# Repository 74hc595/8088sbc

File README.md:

# 8088 Single Board Computer

A minimal single-board computer based on the Intel 8088 processor.
That's the same processor used in the original IBM PC, but this is just a
simple project and doesn't strive for PC/DOS compatibility.

## Specs
- 8088 or compatible CPU in minimal mode (5 MHz with [8088](https://www.jameco.com/z/8088-Major-Brands-IC-8088-8-Bit-HMOS-MPU_52142.html), 8 MHz with 8088-2)
    - Clock oscillator at 3x frequency of CPU clock frequency. For 8 MHz operation, uses a [24 MHz half-can crystal oscillator](https://www.mouser.com/ProductDetail/ECS/ECS-2200B-240?qs=GxOUx7aO6nwQDraMtk%2FyHw%3D%3D)
- 1 MB static RAM (2x [AS6C4008-55PCN](https://www.mouser.com/ProductDetail/Alliance-Memory/AS6C4008-55PCN?qs=%2Fha2pyFaduhSIt5XfNvHc%2FWglHK486gNG4HA%2F19hDPofxZgoFVNuaw%3D%3D))
- 32 KB ROM (1x [AT28C256-15](https://www.jameco.com/z/28C256-15-Major-Brands-IC-28C256-16-EEPROM-256K-Bit-CMOS-Parallel_74843.html))
- FTDI-compatible 5V serial port provided by a [16C550](https://www.jameco.com/shop/ProductDisplay?catalogId=10001&langId=-1&storeId=10001&productId=288809) UART (up to 115200 baud)
- 32 column by 4 row LED display (sixteen PDSP-1881 intelligent displays,
  display board schematic available [here](https://github.com/74hc595/kicad-intelligent-displays))
- Uses five common 74HC chips for glue logic (74HC4017, 74HC132, 74HC573,
  74HC75, 74HC139). Does not require any of the Intel 8200-series support chips.
- 5V power via USB-A connector

## Memory map

```
00000h-7FFFFh - RAM
80000h-FFFFFh - bankable (RAM, ROM, expansion 1, or expansion 2)
```

## I/O map

Only bits 7 and 8 are used for decoding.

```
000h-07Fh - I/O bank 0
    060h-067h - 16550 UART
080h-0FFh - I/O bank 1
100h-17Fh - I/O bank 2
    100h-107h - 128-character display (16x PDSP-1881 or similar)
180h-1FFh - I/O bank 3
```

More info on display decoding:

```
100h-17Fh - Flash RAM
900h-97Fh - UDC Address Register
B00h-B7Fh - UDC RAM
D00h-D7Fh - Control Word Register
F00h-F7Fh - Character RAM
```

## Bank switching and input/output

The modem control lines of the 16550 UART are used as general purpose input and
output lines.

```
~OUT1 - bank select bit 0
~OUT2 - bank select bit 1
~DTR  - general purpose output 0 (LED2)
~RTS  - general purpose output 1 (LED3)
~RI   - general purpose input 0
~DCD  - general purpose input 1
~DSR  - general purpose input 2
~CTS  - general purpose input 3
```

Bank select bits 0 and 1 control which device is mapped into the upper half of
the address space:

```
00 - expansion 1
01 - expansion 2
10 - RAM
11 - ROM (default at power-up)
```

These are controlled by bits 2 and 3 of the 16550's Modem Control Register.
(`64h`)

## Interrupts

The four general-purpose inputs can be set up as inputs by configuring the
16550's Interrupt Enable Register (`61h`). However, this won't be very useful
because the 8088's `~INTA` line is not connected to anything, so when an
interrupt is received, there is no device to place the vector number on the data
bus.

Pressing the `NMI` button will generate a non-maskable interrupt (`INT 04h`).
The button is debounced in hardware.

## Software

Not much here, just enough to test memory and dump the register state. Compiles
with NASM (version 2.14.02 used). Running `make` in the `code/` directory
generates as 32KB binary file. Running `make flash` can be used to burn the
ROM image to an AT28C256 EEPROM chip using a [MiniPro TL866II+](https://www.amazon.com/tl866ii-plus/s?k=tl866ii+plus)
with the [minipro](https://gitlab.com/DavidGriffith/minipro/) utility.

(The TL866II+ is around $60 USD and widely available, if you don't have one,
you should get one!)

1. Power LED will light up.
2. `OUT1` LED will blink four times. (Testing 8 segments of lower RAM)
3. `OUT0` will light.
4. `OUT1` LED will blink four times. (Testing 8 segments of upper RAM)
5. `Hello 8088!` will be printed to the serial port. (115200 8N1)
6. `OUT0` and `OUT1` LEDs will toggle with 50% duty cycle. (verify with scope)
7. Pressing the `NMI` button will print the register state:

```
AX=F001 CS=F000 IP=82E0      NMI
BX=FFF0 DS=F000 SI=82F5     --I-
CX=0000 ES=0000 DI=0024 --------
DX=F202 SS=7000 SP=FFE6 BP=FFFF
```

### API

Interrupt vector `06h` points to the character output routine. If using the
PDSP-1881 LED display, this can be changed to `disp_outch_int` to write to the
display instead of the serial port.

`INT 07h` prints the null-terminated string in `CS:SI`.

`INT 08h` is a rudimentary formatted-output routine. See `output.inc`.

## Future work

Probably none. This was just a quick project and I probably won't work on it
long-term because... honestly, I'm just not a fan of 8086 assembly language and
its weird 16-bit segmented model. Mainly, I had these chips lying around and
wanted to do something with them.

## About

Open hardware, released under the terms of the 3-clause BSD license.

Copyright 2020 Matt Sarnoff.

http://twitter.com/txsector

http://msarnoff.org

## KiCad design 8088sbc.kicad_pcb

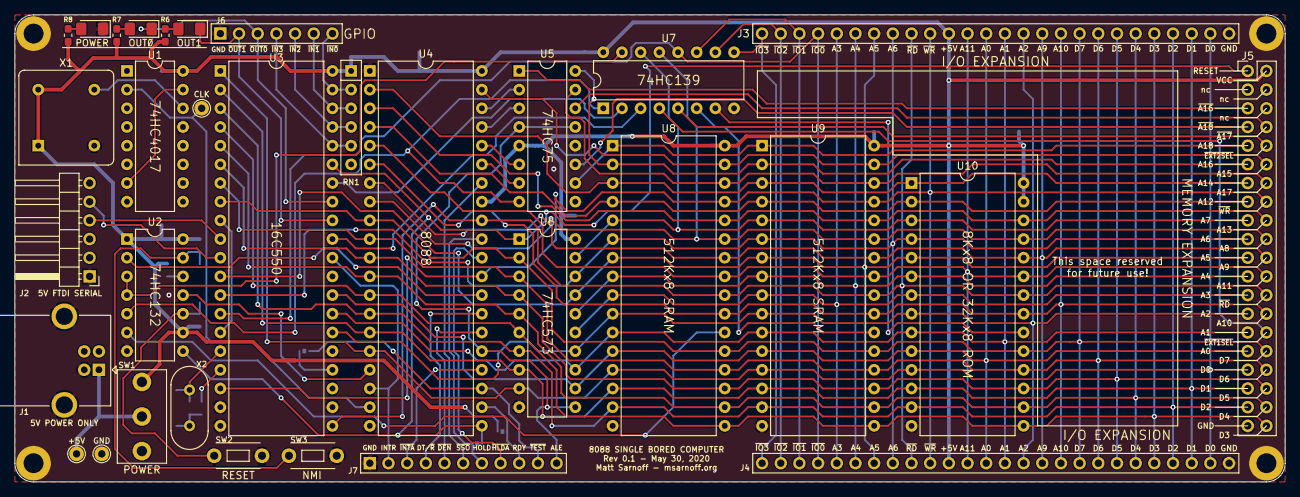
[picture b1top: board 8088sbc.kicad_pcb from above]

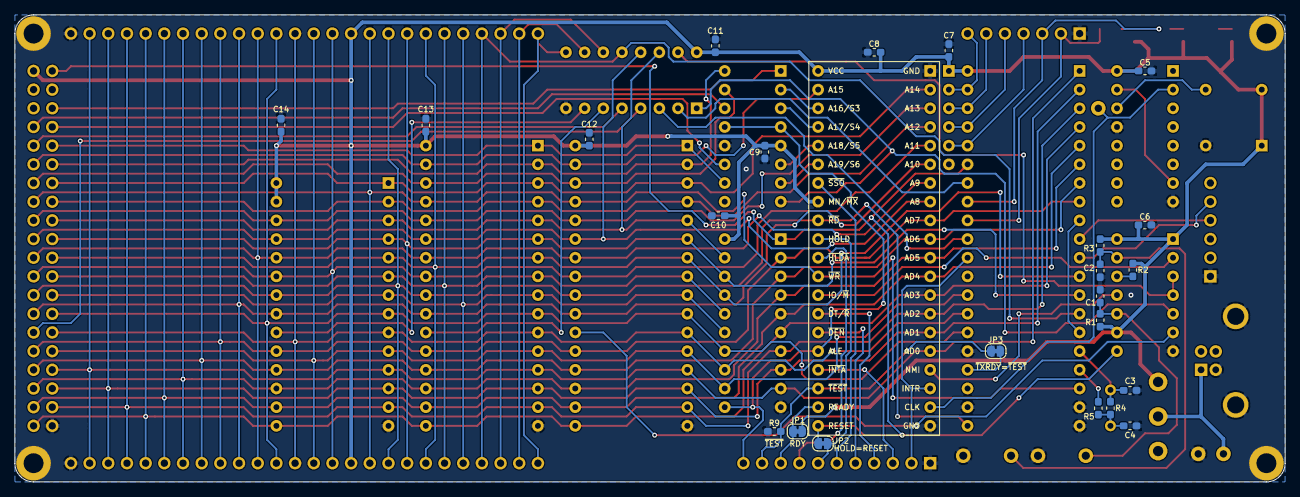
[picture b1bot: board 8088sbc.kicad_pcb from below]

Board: 2 copper layers, 172.7 x 63.5 mm, 55 parts (23 on the bottom side), 87 nets.

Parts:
C1, C2: 4.7uF; R_0603_1608Metric_Pad1.05x0.95mm_HandSolder
C3: 27pF; C_0603_1608Metric_Pad1.05x0.95mm_HandSolder
C4: 47pF; C_0603_1608Metric_Pad1.05x0.95mm_HandSolder
C5, C6, C7, C8, C9, C10, C11, C12, C13, C14: 0.1uF; C_0603_1608Metric_Pad1.05x0.95mm_HandSolder
J1: 5V POWER ONLY; USB_B_OST_USB-B1HSxx_Horizontal
J2: 5V FTDI SERIAL; PinHeader_1x06_P2.54mm_Horizontal
J3, J4: I/O EXP; PinHeader_1x26_P2.54mm_Vertical
J5: MEMORY EXP; PinHeader_2x20_P2.54mm_Vertical
J6: GPIO; PinHeader_1x07_P2.54mm_Vertical
J7: CPU MISC; PinHeader_1x11_P2.54mm_Vertical
JP1, JP2, JP3: SolderJumper_2_Bridged; SolderJumper-2_P1.3mm_Bridged_RoundedPad1.0x1.5mm
LED1: POWER; LED_1206_3216Metric_Pad1.42x1.75mm_HandSolder
LED2: OUT1; LED_1206_3216Metric_Pad1.42x1.75mm_HandSolder
LED3: OUT0; LED_1206_3216Metric_Pad1.42x1.75mm_HandSolder
R1, R2, R3, R9: 10k; R_0603_1608Metric_Pad1.05x0.95mm_HandSolder
R4: 1M; R_0603_1608Metric_Pad1.05x0.95mm_HandSolder
R5: 12k; R_0603_1608Metric_Pad1.05x0.95mm_HandSolder
R6, R7, R8: 330; R_0603_1608Metric_Pad1.05x0.95mm_HandSolder
RN1: 10k; R_Array_SIP6
SW1: POWER; SW_Slide_1P2T_Cylewet_ CYT1107
SW2: RESET; SW_PUSH_3x6mm
SW3: NMI; SW_PUSH_3x6mm
TP1: +5V; TestPoint_THTPad_D2.0mm_Drill1.0mm
TP2: GND; TestPoint_THTPad_D2.0mm_Drill1.0mm
TP3: CLK; TestPoint_THTPad_D2.0mm_Drill1.0mm
U1: 74HC4017; DIP-16_W7.62mm
U2: 74HC132; DIP-14_W7.62mm
U3: 16550; DIP-40_W15.24mm
U4: MBL8088-2; DIP-40_W15.24mm
U5: 74HC75; DIP-16_W7.62mm
U6: 74HC573; DIP-20_W7.62mm
U7: 74HC139; DIP-16_W7.62mm
U8, U9: AS6C4008-55PCN; DIP-32_W15.24mm
U10: 28C256; DIP-28_W15.24mm
X1: 20.0 MHz; Oscillator_DIP-8
X2: 1.8432MHz; Crystal_HC49-U_Vertical

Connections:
/A0: J3.13, J4.13, J5.31, U3.28, U6.12, U8.12, U9.12, U10.10
/A1: J3.14, J4.14, J5.29, U3.27, U6.13, U8.11, U9.11, U10.9
/A2: J3.15, J4.15, J5.27, U3.26, U6.14, U8.10, U9.10, U10.8
/A3: J3.5, J4.5, J5.25, U6.15, U8.9, U9.9, U10.7
/A4: J3.6, J4.6, J5.23, U6.16, U8.8, U9.8, U10.6
/A5: J3.7, J4.7, J5.21, U3.12, U6.17, U8.7, U9.7, U10.5
/A6: J3.8, J4.8, J5.19, U3.13, U6.18, U8.6, U9.6, U10.4
/A7: J5.17, U6.19, U7.14, U8.5, U9.5, U10.3
/A8: J5.20, U4.8, U7.13, U8.27, U9.27, U10.25
/A9: J3.16, J4.16, J5.22, U4.7, U8.26, U9.26, U10.24
/A10: J3.17, J4.17, J5.28, U4.6, U8.23, U9.23, U10.21
/A11: J3.12, J4.12, J5.24, U4.5, U8.25, U9.25, U10.23
/A12: J5.15, U4.4, U8.4, U9.4, U10.2
/A13: J5.18, U4.3, U8.28, U9.28, U10.26
/A14: J5.13, U4.2, U8.3, U9.3, U10.1
/A15: J5.12, U4.39, U8.31, U9.31
/A16: J5.11, U5.16, U8.2, U9.2
/A17: J5.14, U5.15, U8.30, U9.30
/A18: J5.9, U5.10, U8.1, U9.1
/AD0: J3.25, J4.25, J5.33, U3.1, U4.16, U6.9, U8.13, U9.13, U10.11
/AD1: J3.24, J4.24, J5.35, U3.2, U4.15, U6.8, U8.14, U9.14, U10.12
/AD2: J3.23, J4.23, J5.37, U3.3, U4.14, U6.7, U8.15, U9.15, U10.13
/AD3: J3.22, J4.22, J5.40, U3.4, U4.13, U6.6, U8.17, U9.17, U10.15
/AD4: J3.21, J4.21, J5.38, U3.5, U4.12, U6.5, U8.18, U9.18, U10.16
/AD5: J3.20, J4.20, J5.36, U3.6, U4.11, U6.4, U8.19, U9.19, U10.17
/AD6: J3.19, J4.19, J5.34, U3.7, U4.10, U6.3, U8.20, U9.20, U10.18
/AD7: J3.18, J4.18, J5.32, U3.8, U4.9, U6.2, U8.21, U9.21, U10.19
/ALE: J7.11, U4.25, U5.4, U5.13, U6.11
/BANK0: U3.34, U7.2
/BANK1: U3.31, U7.3
/CLK: TP3.1, U1.2, U4.19
/DT,~R: J7.4, U4.27
/HOLD: J7.7, JP2.2, U4.31
/INTR: J7.2, U3.30, U4.18
/M: U2.3, U2.4, U7.15
/NMI: U2.11, U4.17
/READY: J7.9, JP1.2, U4.22
/RESET: J5.1, JP2.1, U2.8, U3.35, U4.21, U6.1
/RXD: J2.5, U3.11
/TXD: J2.4, U3.10
/~A16: J5.5, U5.1
/~A17: J5.8, U5.14
/~A18: J5.7, U5.11
/~A19: U2.5, U5.8, U7.1
/~DEN: J7.5, U4.26
/~EXT1SEL: J5.30, U7.4
/~EXT2SEL: J5.10, U7.5
/~EXTNMI: R2.1, U2.12
/~GPI0: J6.7, RN1.2, U3.39
/~GPI1: J6.6, RN1.3, U3.38
/~GPI2: J6.5, RN1.4, U3.37
/~GPI3: J6.4, RN1.5, U3.36
/~GPO0: J6.3, LED3.1, U3.33
/~GPO1: J6.2, LED2.1, U3.32
/~HLDA: J7.8, U4.30
/~INTA: J7.3, U4.24
/~IOSEL0: J3.4, J4.4, U3.14, U7.12
/~IOSEL1: J3.3, J4.3, U7.11
/~IOSEL2: J3.2, J4.2, U7.10
/~IOSEL3: J3.1, J4.1, U7.9
/~LRAMSEL: U2.6, U8.22
/~M: U2.2, U4.28
/~RD: J3.9, J4.9, J5.26, U3.21, U4.32, U8.24, U9.24, U10.22
/~SSO: J7.6, U4.34
/~TEST: J7.10, JP3.2, R9.2, U4.23
/~URAMSEL: U7.6, U9.22
/~UROMSEL: U7.7, U10.20
/~WR: J3.10, J4.10, J5.16, U3.18, U4.29, U8.29, U9.29
GND: C1.2, C2.2, C3.2, C4.2, C5.2, C6.2, C7.2, C8.2, C9.2, C10.2, C11.2, C12.2, C13.2, C14.2, J1.4, J1.5, J2.1, J3.26, J4.26, J5.39, J6.1, J7.1, LED1.1, R9.1, SW2.1, SW3.1, TP2.1, U1.8, U1.13, U2.7, U3.19, U3.20, U3.22, U3.25, U4.1, U4.20, U5.12, U6.10, U7.8, U8.16, U9.16, U10.14, X1.4
unnamed: C1.1, R1.1, SW2.2, U2.10
unnamed: C2.1, R3.1, SW3.2, U2.13
unnamed: C3.1, R4.2, U3.16, X2.2
unnamed: C4.1, R4.1, R5.2, X2.1
unnamed: JP3.1, U3.24
unnamed: LED1.2, R8.1
unnamed: LED2.2, R6.1
unnamed: LED3.2, R7.1
unnamed: R5.1, U3.17
unnamed: U1.14, X1.5
unnamed: U1.7, U1.15
unnamed: U3.9, U3.15
unnamed: U4.35, U5.7
unnamed: U4.36, U5.6
unnamed: U4.37, U5.3
unnamed: U4.38, U5.2
VBUS: J1.1, SW1.2, TP1.1
VCC: C5.1, C6.1, C7.1, C8.1, C9.1, C10.1, C11.1, C12.1, C13.1, C14.1, J3.11, J4.11, J5.2, JP1.1, R1.2, R2.2, R3.2, R6.2, R7.2, R8.2, RN1.1, SW1.1, U1.16, U2.1, U2.9, U2.14, U3.40, U4.33, U4.40, U5.5, U6.20, U7.16, U8.32, U9.32, U10.27, U10.28, X1.1, X1.8

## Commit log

2020-05-31 add pdf schematic
